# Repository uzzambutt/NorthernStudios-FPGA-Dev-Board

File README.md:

# NorthernStudios FPGA Dev Board

**Designed by Muhammad Uzzam Butt // Made for Macondo**

---

## Overview
This FPGA Devboard is designed in KiCad v9.0 and is built around the Gowin GW1NSR-4C, a hybrid FPGA chip containing an embedded ARM Cortex-M3 microcontroller. 

---

## Hardware Specifications

### FPGA Core
* FPGA Chip: Gowin GW1NSR-4C (specifically GW1NSR-4C_MG64P in an MBGA64 package)
* Embedded ARM Cortex-M3 hard core processor
* 4,608 Look Up Tables (LUTs)
* 3,456 Flip Flops (FFs)
* Embedded block SRAM and internal Flash memory

### Power Delivery
* Input Source: USB Type-C (+5V VBUS)
* Core Regulator: AP2112K 1.2 LDO (600mA) generating +1.2V for the FPGA core
* I/O and Peripheral Regulator: AP2112K-3.3 LDO (600mA) generating +3.3V for I/O banks, clocking, and UART bridge
* Decoupling: Optimized bypass capacitor networks (0.1uF and 10uF) on each power pin to ensure low-noise rails

### Interfaces and Connectivity
* USB Connector: USB 2.0 Type-C interface
* Serial Communication: CP2102N USB-to-UART bridge for programming and debug output
* Main Breakout: Dual 24-pin headers for breadboard compatibility, exposing FPGA I/Os, system power, and ground pins
* Accessory Port: 6-pin PMOD style header for SPI, I2C, or UART hardware attachments

### Clocking and User Controls
* Clock Oscillator: SG-8002CE (24.0000 MHz) active crystal oscillator
* User Controls: Push buttons for system reset and user input
* Visual Indicators: Status and user-configurable LEDs
* Level Translation: BSS138 N-channel MOSFET circuit for voltage-level switching

---

## Bill of Materials (BOM)

A complete list of components required to assemble the dev board is detailed in the table below (sourced from [bom.csv](file:///D:/NS%20FPGA/hardware/jlcpcb/production_files/bom.csv)):

| Comment | Designator | Footprint | LCSC | Quantity |
| :--- | :--- | :--- | :--- | :--- |
| 0.1uF | C1, C4, C6 | C_0402_1005Metric | C141382 | 3 |
| 0.1uF | C11, C12, C13, C14, C15, C16, C17 | C_0201_0603Metric | C66938 | 7 |
| 10k | R12, R3, R9 | R_0402_1005Metric | C25725 | 3 |
| 10uF | C10, C7, C8, C9 | C_0402_1005Metric | C15525 | 4 |
| 1k | R10 | R_0201_0603Metric | C131396 | 1 |
| 22.1k | R4 | R_0201_0603Metric | C423662 | 1 |
| 330 | R11 | R_0201_0603Metric | C274872 | 1 |
| 4.7k | R7, R8 | R_0201_0603Metric | C142008 | 2 |
| 4.7uF | C2, C3, C5 | C_0402_1005Metric | C23733 | 3 |
| 47.5k | R5 | R_0201_0603Metric | C166179 | 1 |
| 5.1k | R1, R2 | R_0402_1005Metric | C25905 | 2 |
| AP2112K-1.2 | U4 | SOT-23-5 | C49451994 | 1 |
| AP2112K-3.3 | U3 | SOT-23-5 | C3021085 | 1 |
| BSS138 | Q1 | SOT-23 | C52895 | 1 |
| CP2102N-Axx-xQFN24 | U2 | QFN-24-1EP_4x4mm_P0.5mm_EP2.6x2.6mm | C969151 | 1 |
| LED | D1, D2 | LED_0201_0603Metric | C3646922 | 2 |
| R22 | R6 | R_0201_0603Metric | C142011 | 1 |
| SG-8002CE(24.0000M) | Y1 | Oscillator_SMD_SeikoEpson_SG8002CE-4Pin_3.2x2.5mm | C390322 | 1 |
| SW_Push | SW1 | SW_SPST_EVQP2_ShortPushTravel_H2.1mm | C2915174 | 1 |
| USB_C_Receptacle_USB2.0_14P | J1 | USB_C_Receptacle_HCTL_HC-TYPE-C-16P-01A | C165948 | 1 |
| GW1NSR-4C-MG64P | U1 | BGA-64_8x8_4.2x4.2mm | Gowin GW1NSR-4C-MG64P | 1 |
| TestPoint | TP4 | TestPoint_Pad_D1.0mm | | 1 |
| TestPoint | TP3 | TestPoint_Pad_D1.0mm | | 1 |
| TestPoint | TP2 | TestPoint_Pad_D1.0mm | | 1 |
| TestPoint | TP1 | TestPoint_Pad_D1.0mm | | 1 |
| Jtag PIN | J4 | PinHeader_1x06_P2.54mm_Vertical | | 1 |
| Conn_01x24_Pin | J3 | PinHeader_1x24_P2.54mm_Vertical | | 1 |
| Conn_01x24_Pin | J2 | PinHeader_1x24_P2.54mm_Vertical | | 1 |

---

## KiCad Setup

1. Open the project using KiCad v9.0 or later by selecting [NS FPGA.kicad_pro](file:///D:/NS%20FPGA/hardware/NS%20FPGA.kicad_pro).
2. The Gowin FPGA symbol is located in the local library file [gowin_fpga.lib](file:///D:/NS%20FPGA/gowin_fpga.lib). Make sure it is mapped correctly in your KiCad symbol library table if you plan to edit the schematics.

---

## License

This project is open-source hardware licensed under the [MIT License](LICENSE).

---

*Designed by Muhammad Uzzam Butt // Made for Macondo*

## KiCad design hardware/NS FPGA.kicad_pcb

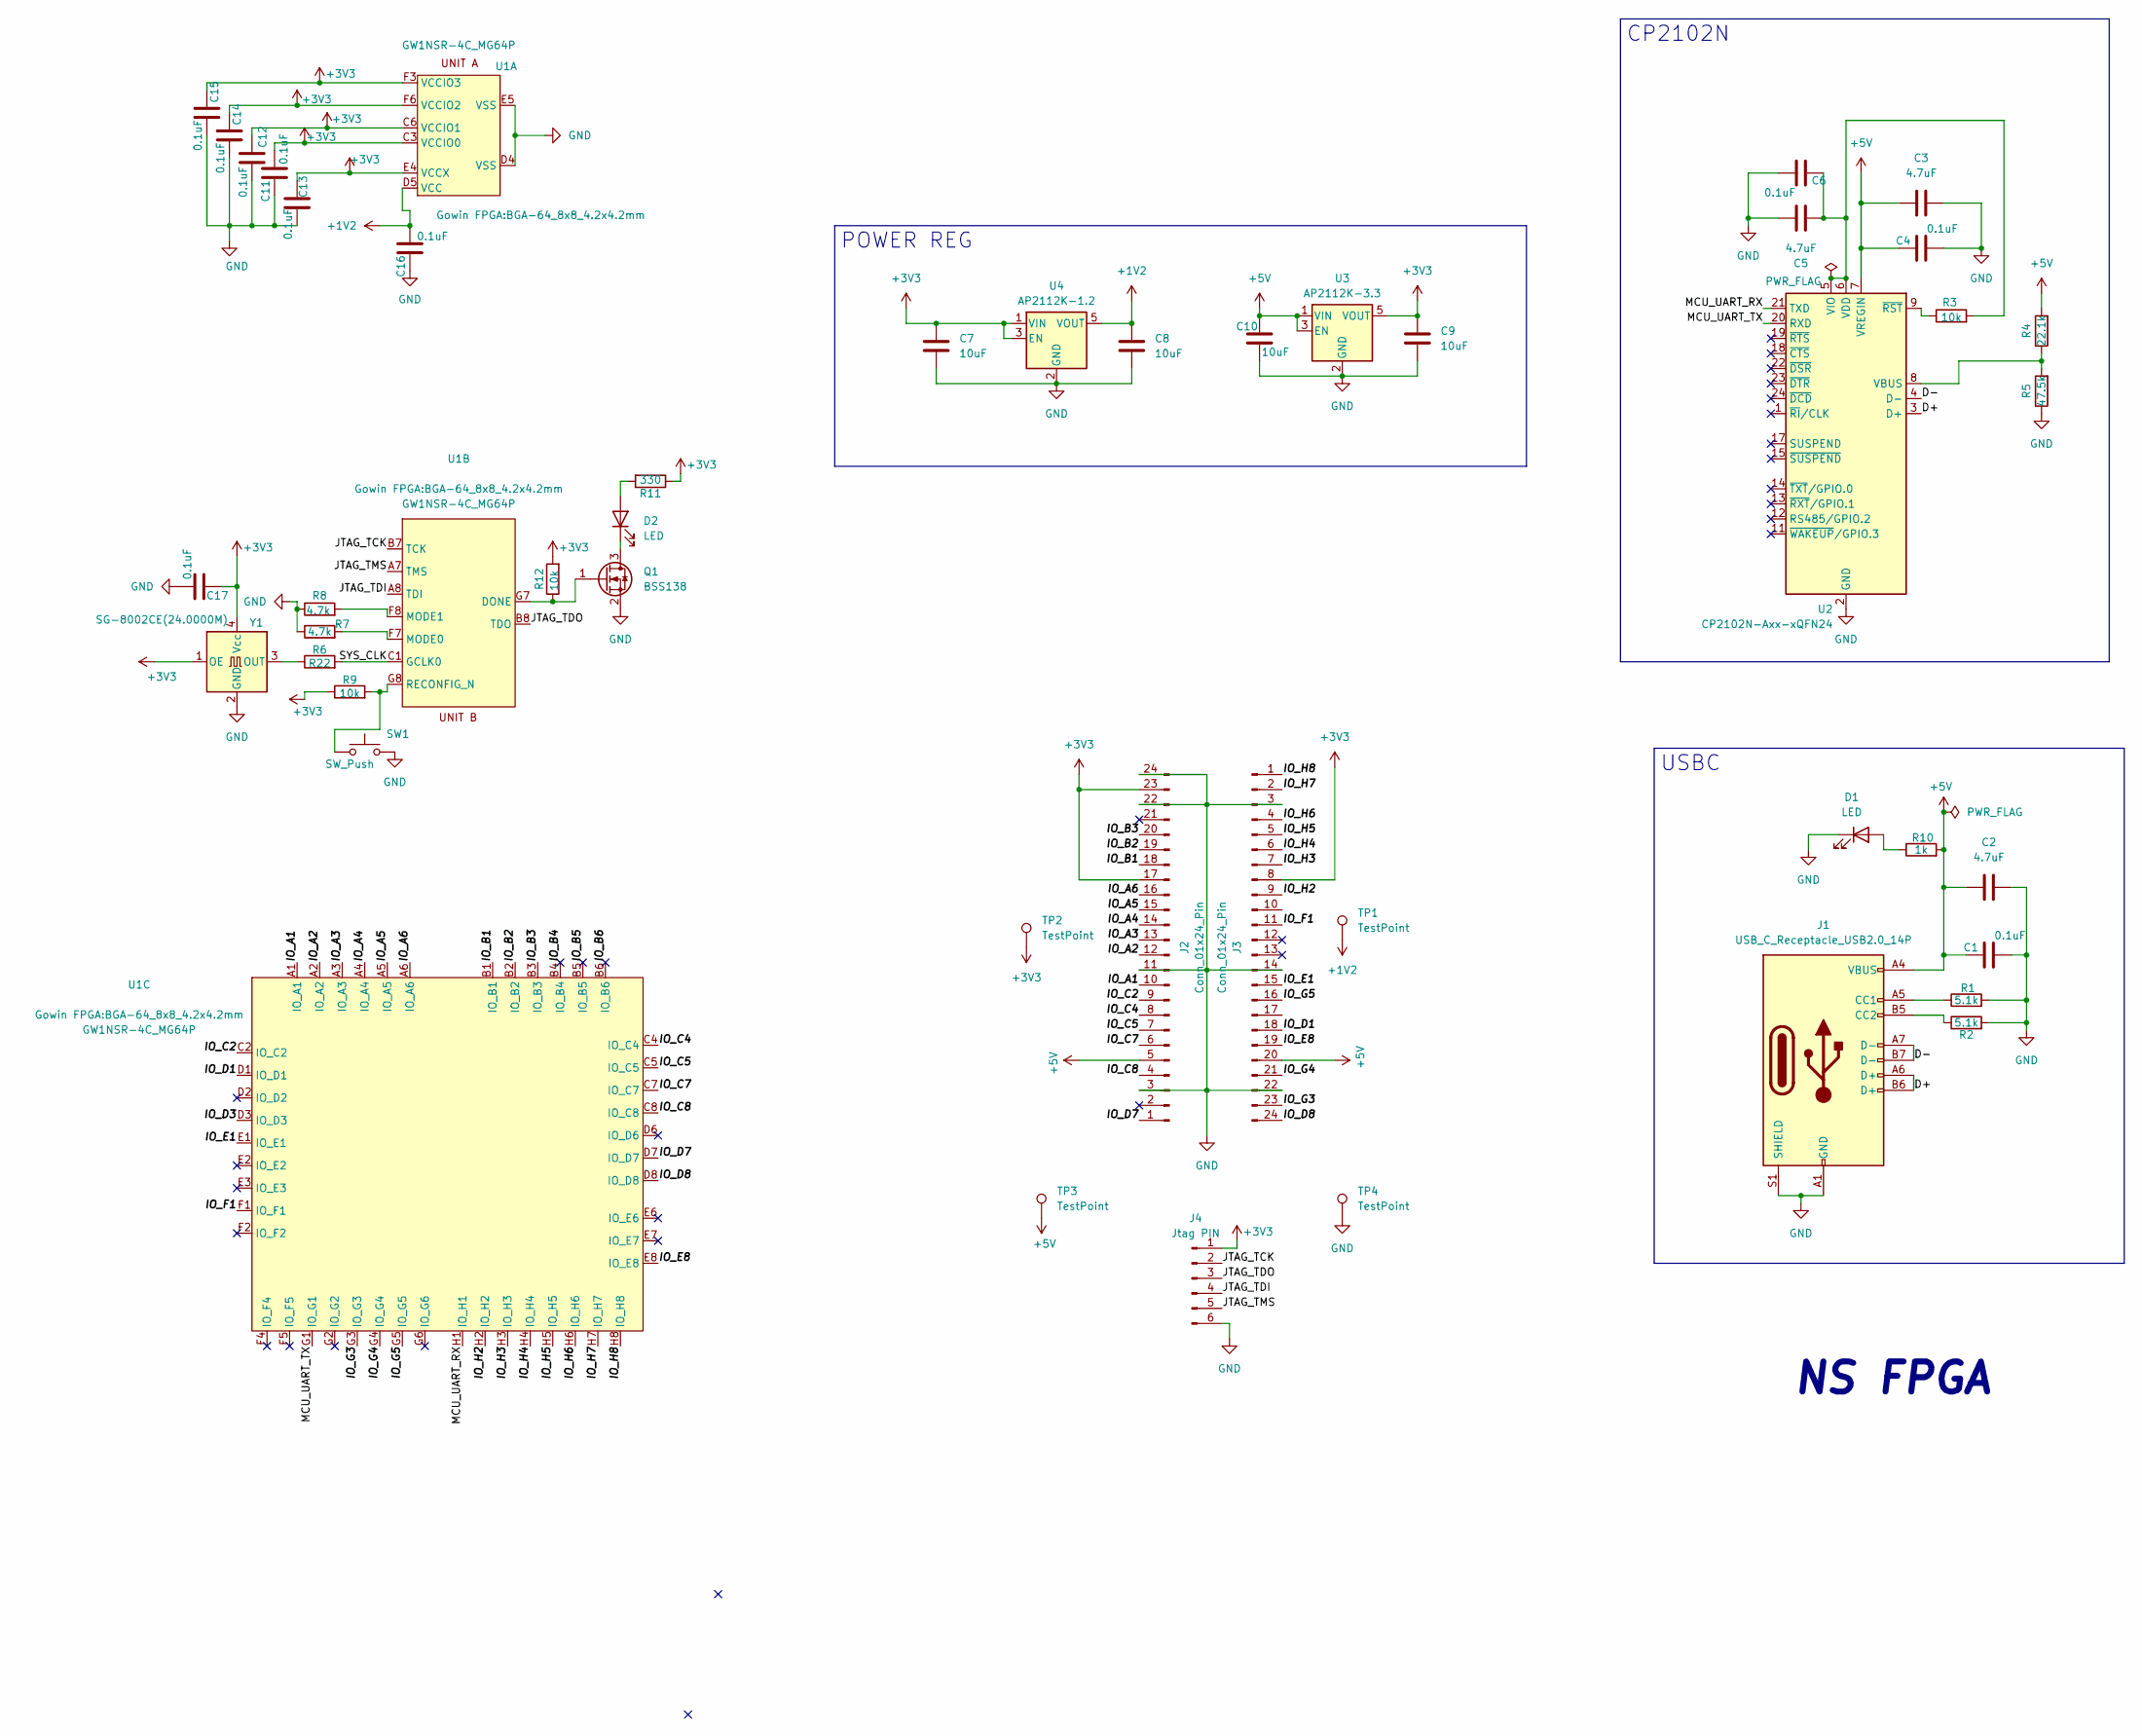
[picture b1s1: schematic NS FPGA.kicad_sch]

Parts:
C1, C4, C6: 0.1uF; C_0402_1005Metric
C2, C3, C5: 4.7uF; C_0402_1005Metric
C7, C8, C9, C10: 10uF; C_0402_1005Metric
C11, C12, C13, C14, C15, C16, C17: 0.1uF; C_0201_0603Metric
D1, D2: LED; LED_0201_0603Metric
J1: USB_C_Receptacle_USB2.0_14P; USB_C_Receptacle_HCTL_HC-TYPE-C-16P-01A
J2, J3: Conn_01x24_Pin; PinHeader_1x24_P2.54mm_Vertical
J4: Jtag PIN; PinHeader_1x06_P2.54mm_Vertical
Q1: BSS138; SOT-23
R1, R2: 5.1k; R_0402_1005Metric
R3, R9, R12: 10k; R_0402_1005Metric
R4: 22.1k; R_0201_0603Metric
R5: 47.5k; R_0201_0603Metric
R6: R22; R_0201_0603Metric
R7, R8: 4.7k; R_0201_0603Metric
R10: 1k; R_0201_0603Metric
R11: 330; R_0201_0603Metric
SW1: SW_Push; SW_SPST_EVQP2_ShortPushTravel_H2.1mm
TP1, TP2, TP3, TP4: TestPoint; TestPoint_Pad_D1.0mm
U1: BGA-64_8x8_4.2x4.2mm
U2: CP2102N-Axx-xQFN24; QFN-24-1EP_4x4mm_P0.5mm_EP2.6x2.6mm
U3: AP2112K-3.3; SOT-23-5
U4: AP2112K-1.2; SOT-23-5
Y1: SG-8002CE(24.0000M); Oscillator_SMD_SeikoEpson_SG8002CE-4Pin_3.2x2.5mm

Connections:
+1V2: C8.1, C16.2, TP1.1, U1.D5 (VCC), U4.5 (VOUT)
+3V3: C7.1, C9.1, C11.2, C12.1, C13.1, C14.1, C15.1, C17.1, J2.17, J2.23, J3.8, J4.1, R9.1, R11.1, R12.2, TP2.1, U1.C3 (VCCIO0), U1.C6 (VCCIO1), U1.E4 (VCCX), U1.F3 (VCCIO3), U1.F6 (VCCIO2), U3.5 (VOUT), U4.1 (VIN), U4.3 (EN), Y1.1 (OE), Y1.4 (Vcc)
+5V: C1.1, C2.1, C3.1, C4.1, C10.1, J1.A4 (VBUS), J1.A9 (VBUS), J1.B4 (VBUS), J1.B9 (VBUS), J2.5, J3.20, R4.2, R10.2, TP3.1, U2.7 (VREGIN), U3.1 (VIN), U3.3 (EN)
/D+: J1.A6 (D+), J1.B6 (D+), U2.3 (D+)
/D-: J1.A7 (D-), J1.B7 (D-), U2.4 (D-)
/IO_A1: J2.10, U1.A1 (IO_A1)
/IO_A2: J2.12, U1.A2 (IO_A2)
/IO_A3: J2.13, U1.A3 (IO_A3)
/IO_A4: J2.14, U1.A4 (IO_A4)
/IO_A5: J2.15, U1.A5 (IO_A5)
/IO_A6: J2.16, U1.A6 (IO_A6)
/IO_B1: J2.18, U1.B1 (IO_B1)
/IO_B2: J2.19, U1.B2 (IO_B2)
/IO_B3: J2.20, U1.B3 (IO_B3)
/IO_B4: U1.B4 (IO_B4)
/IO_B5: U1.B5 (IO_B5)
/IO_B6: U1.B6 (IO_B6)
/IO_C2: J2.9, U1.C2 (IO_C2)
/IO_C4: J2.8, U1.C4 (IO_C4)
/IO_C5: J2.7, U1.C5 (IO_C5)
/IO_C7: J2.6, U1.C7 (IO_C7)
/IO_C8: J2.4, U1.C8 (IO_C8)
/IO_D1: J3.18, U1.D1 (IO_D1)
/IO_D3: U1.D3 (IO_D3)
/IO_D7: J2.1, U1.D7 (IO_D7)
/IO_D8: J3.24, U1.D8 (IO_D8)
/IO_E1: J3.15, U1.E1 (IO_E1)
/IO_E8: J3.19, U1.E8 (IO_E8)
/IO_F1: J3.11, U1.F1 (IO_F1)
/IO_G3: J3.23, U1.G3 (IO_G3)
/IO_G4: J3.21, U1.G4 (IO_G4)
/IO_G5: J3.16, U1.G5 (IO_G5)
/IO_H2: J3.9, U1.H2 (IO_H2)
/IO_H3: J3.7, U1.H3 (IO_H3)
/IO_H4: J3.6, U1.H4 (IO_H4)
/IO_H5: J3.5, U1.H5 (IO_H5)
/IO_H6: J3.4, U1.H6 (IO_H6)
/IO_H7: J3.2, U1.H7 (IO_H7)
/IO_H8: J3.1, U1.H8 (IO_H8)
/JTAG_TCK: J4.2, U1.B7 (TCK)
/JTAG_TDI: J4.4, U1.A8 (TDI)
/JTAG_TDO: J4.3, U1.B8 (TDO)
/JTAG_TMS: J4.5, U1.A7 (TMS)
/MCU_UART_RX: U1.H1 (IO_H1), U2.21 (TXD)
/MCU_UART_TX: U1.G1 (IO_G1), U2.20 (RXD)
/SYS_CLK: R6.2, U1.C1 (GCLK0)
GND: C1.2, C2.2, C3.2, C4.2, C5.2, C6.2, C7.2, C8.2, C9.2, C10.2, C11.1, C12.2, C13.2, C14.2, C15.2, C16.1, C17.2, D1.1 (K), J1.A1 (GND), J1.A12 (GND), J1.B1 (GND), J1.B12 (GND), J1.S1 (SHIELD), J2.3, J2.11, J2.22, J2.24, J3.3, J3.14, J3.22, J4.6, Q1.2 (S), R1.2, R2.2, R5.1, R7.1, R8.1, SW1.2, TP4.1, U1.D4 (VSS), U1.E5 (VSS), U2.2 (GND), U2.25 (GND), U3.2 (GND), U4.2 (GND), Y1.2 (GND)
unnamed: D1.2 (A), R10.1
unnamed: D2.2 (A), R11.2
unnamed: D2.1 (K), Q1.3 (D)
unnamed: J1.A5 (CC1), R1.1
unnamed: J1.B5 (CC2), R2.1
unnamed: Q1.1 (G), R12.1, U1.G7 (DONE)
unnamed: R7.2, U1.F7 (MODE0)
unnamed: R8.2, U1.F8 (MODE1)
unnamed: R9.2, SW1.1, U1.G8 (RECONFIG_N)
unnamed: R4.1, R5.2, U2.8 (VBUS)
unnamed: C5.1, C6.1, R3.2, U2.5 (VIO), U2.6 (VDD)
unnamed: R3.1, U2.9 (~RST)
unnamed: R6.1, Y1.3 (OUT)

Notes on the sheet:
NS FPGA
POWER REG
USBC
CP2102N

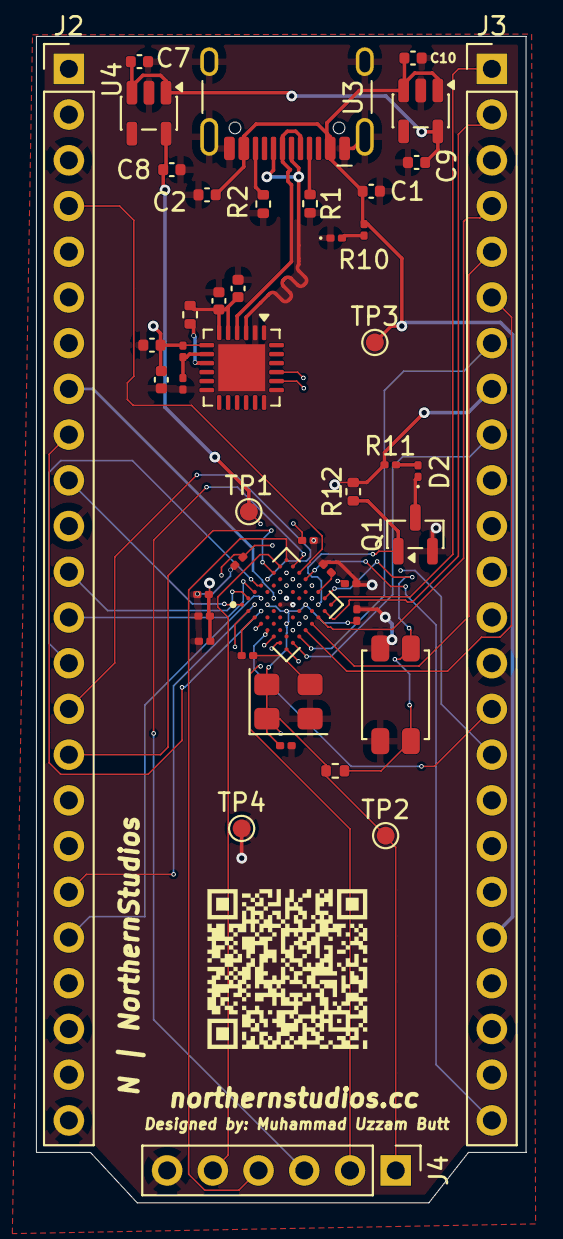
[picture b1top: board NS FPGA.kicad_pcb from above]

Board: 6 copper layers, 27.2 x 64.8 mm, 46 parts (0 on the bottom side), 56 nets.

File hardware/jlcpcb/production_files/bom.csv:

Comment,Designator,Footprint,LCSC,Quantity
0.1uF,"C1,C4,C6",C_0402_1005Metric,C141382,3
0.1uF,"C11,C12,C13,C14,C15,C16,C17",C_0201_0603Metric,C66938,7
10k,"R12,R3,R9",R_0402_1005Metric,C25725,3
10uF,"C10,C7,C8,C9",C_0402_1005Metric,C15525,4
1k,R10,R_0201_0603Metric,C131396,1
22.1k,R4,R_0201_0603Metric,C423662,1
330,R11,R_0201_0603Metric,C274872,1
4.7k,"R7,R8",R_0201_0603Metric,C142008,2
4.7uF,"C2,C3,C5",C_0402_1005Metric,C23733,3
47.5k,R5,R_0201_0603Metric,C166179,1
5.1k,"R1,R2",R_0402_1005Metric,C25905,2
AP2112K-1.2,U4,SOT-23-5,C49451994,1
AP2112K-3.3,U3,SOT-23-5,C3021085,1
BSS138,Q1,SOT-23,C52895,1
CP2102N-Axx-xQFN24,U2,QFN-24-1EP_4x4mm_P0.5mm_EP2.6x2.6mm,C969151,1
LED,"D1,D2",LED_0201_0603Metric,C3646922,2
R22,R6,R_0201_0603Metric,C142011,1
SG-8002CE(24.0000M),Y1,Oscillator_SMD_SeikoEpson_SG8002CE-4Pin_3.2x2.5mm,C390322,1
SW_Push,SW1,SW_SPST_EVQP2_ShortPushTravel_H2.1mm,C2915174,1
USB_C_Receptacle_USB2.0_14P,J1,USB_C_Receptacle_HCTL_HC-TYPE-C-16P-01A,C165948,1
GW1NSR-4C-MG64P,U1,BGA-64_8x8_4.2x4.2mm,Gowin GW1NSR-4C-MG64P,1
TestPoint,TP4,TestPoint_Pad_D1.0mm,,1
TestPoint,TP3,TestPoint_Pad_D1.0mm,,1
TestPoint,TP2,TestPoint_Pad_D1.0mm,,1
TestPoint,TP1,TestPoint_Pad_D1.0mm,,1
Jtag PIN,J4,PinHeader_1x06_P2.54mm_Vertical,,1
Conn_01x24_Pin,J3,PinHeader_1x24_P2.54mm_Vertical,,1
Conn_01x24_Pin,J2,PinHeader_1x24_P2.54mm_Vertical,,1

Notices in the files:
README.md:
License: MIT
